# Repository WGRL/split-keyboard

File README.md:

# split-keyboard
Split keyboard with ble and usb. Custom pcb based on nrf52840 mcu module with specific firmware written in  C (Zephyr)

# Firmware
All the firmware is stored in `software` directory. It also contains all the configs for Zephyr, Kconfig, CMAKE, scripts etc.
The source code is stored in `software/src`.

The right side connects to the left one using Bluetooth. It sends the hid codes of clicked keys with approximately 12 ms intervals.
The left side takes together keys clicked on left and right side and sends it to the PC using eithter Bluetooth or USB.
USB and Bluetooth are automatically switched. If the USB connection is detected it is a chosen communication method. If there is no USB connection then left side starts Bluetooth advertising or automatically connects to the PC if there is bonding already.

The name of the device is automatically WGRL_KEYBOARD, but you can change it in `software/config/prj_left.conf` in the `# Names` section.  

# Compilation
To program the mcu you use eithter
`./scripts/run.sh left` or `./scripts/run.sh right` 
depending on the side

# Electronics
The files for printed PCBs are stored in `hardware` directory.

This is for personal use so note that the boards don't have any ESD, reverse polarity, overvoltage protection etc.
Also it lacks extra capacitor to sustain battery voltage.

# PCB
Printed PCBs. The files are in `hardware` directory. They are based on only THT elements for easier soldering.

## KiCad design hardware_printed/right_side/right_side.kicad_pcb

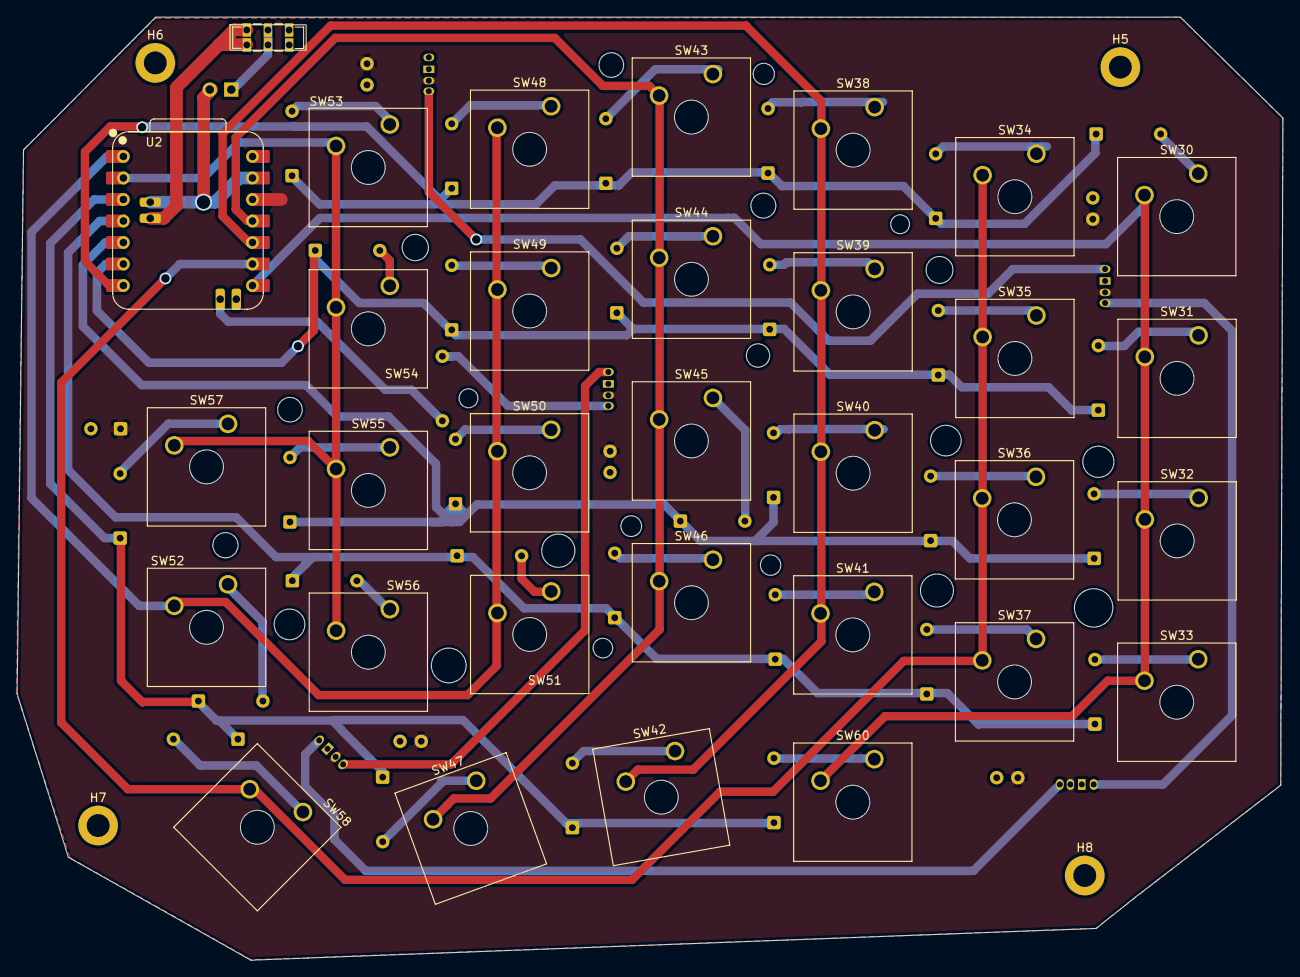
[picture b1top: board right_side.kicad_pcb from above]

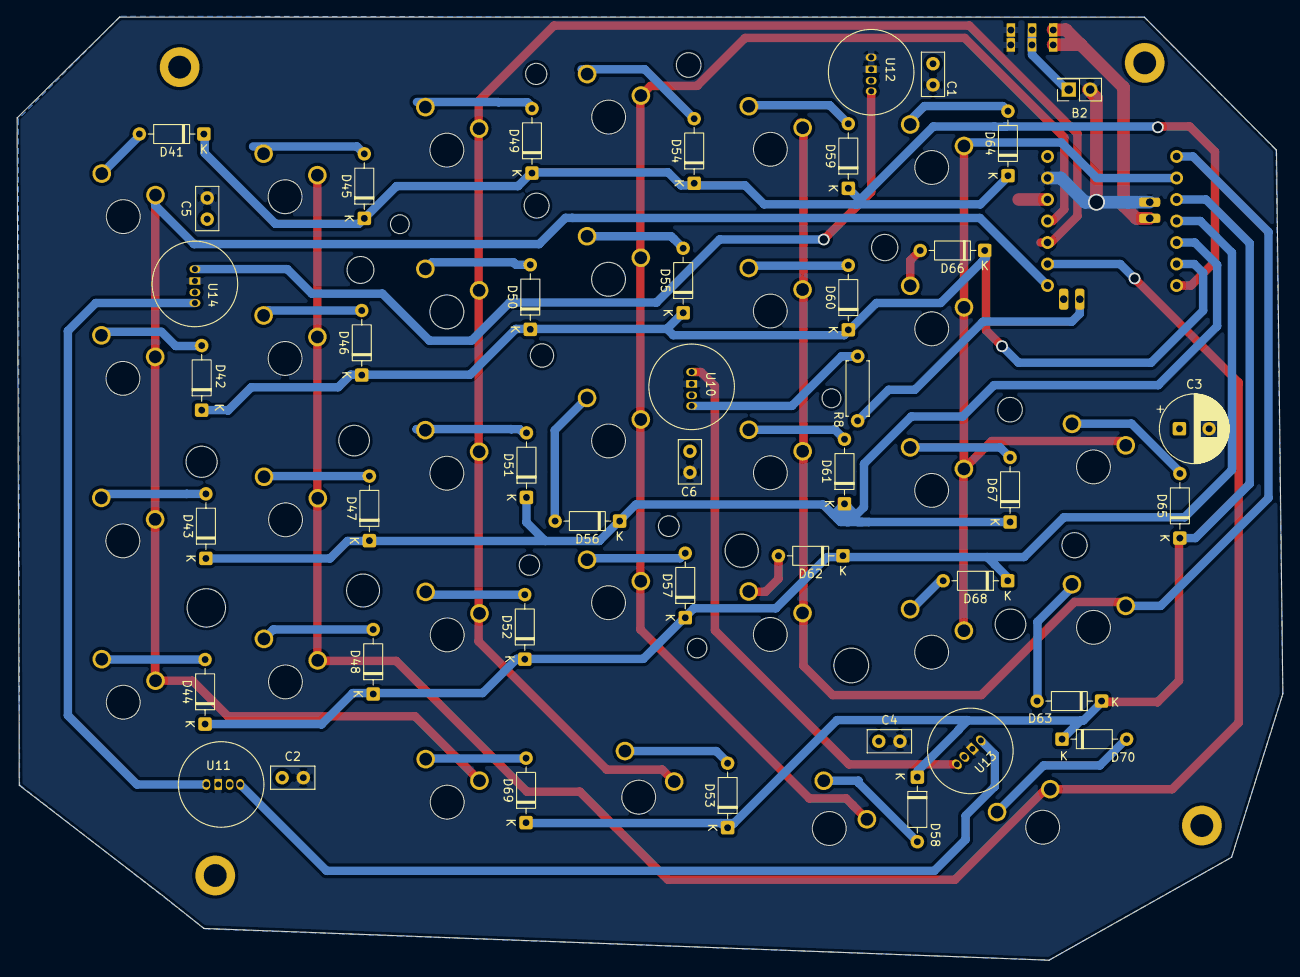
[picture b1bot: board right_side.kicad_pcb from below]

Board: 2 copper layers, 149.4 x 111.3 mm, 79 parts (43 on the bottom side), 51 nets.

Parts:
B2: Li-Pol Battery; PinSocket_2x01_P2.54mm_Vertical
C1, C2, C4, C5, C6: 100n; C_Disc_D5.0mm_W2.5mm_P2.50mm
C3: 470u; CP_Radial_D8.0mm_P3.50mm
D41, D42, D43, D44, D45, D46, D47, D48, D49, D50, D51, D52, D53, D54, D55, D56, D57, D58, D59, D60, D61, D62, D63, D64, D65, D66, D67, D68, D69, D70: 1N4148; D_DO-35_SOD27_P7.62mm_Horizontal
H5, H6, H7, H8: MountingHole; MountingHole_2.7mm_M2.5_DIN965_Pad
R8: 100; R_Axial_DIN0207_L6.3mm_D2.5mm_P7.62mm_Horizontal
SW30, SW31, SW32, SW33, SW34, SW35, SW36, SW37, SW38, SW39, SW40, SW41, SW42, SW43, SW44, SW45, SW46, SW47, SW48, SW49, SW50, SW51, SW52, SW53, SW54, SW55, SW56, SW57, SW58, SW60: SW_Push; SW_Cherry_MX_1.00u_Plate
SW_POW2: SS22T25; slider
U2: XIAO-nRF52840-DIP_SMD
U10, U11, U12, U13, U14: PL9823; PL9823-F8

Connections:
3V3: C1.1, C2.1, C3.1, C4.1, C5.1, C6.1, U2.12 (3V3), U10.3 (VDD), U11.3 (VDD), U12.3 (VDD), U13.3 (VDD), U14.3 (VDD)
/LED DIN: R8.1, U2.21 (NFC_0.09)
/col0: SW30.2, SW31.2, SW32.2, SW33.2, SW60.2, U2.8 (P1.12_D7_RX)
/col1: SW34.2, SW35.2, SW36.2, SW37.2, SW58.2, U2.9 (P1.13_D8_SCK)
/col2: SW38.2, SW39.2, SW40.2, SW41.2, SW42.2, U2.10 (P1.14_D9_MISO)
/col3: SW43.2, SW44.2, SW45.2, SW46.2, SW47.2, U2.11 (P1.15_D10_MOSI)
/col4: SW48.2, SW49.2, SW50.2, SW51.2, SW52.2, U2.1 (P0.02_A0_D0)
/col5: SW53.2, SW54.2, SW55.2, SW56.2, SW57.2, U2.2 (P0.03_A1_D1)
/row0: D41.1 (K), D45.1 (K), D49.1 (K), D54.1 (K), D59.1 (K), D64.1 (K), U2.7 (P1.11_D6_TX)
/row1: D42.1 (K), D46.1 (K), D50.1 (K), D55.1 (K), D60.1 (K), D66.1 (K), U2.6 (P0.05_A5_D5_SCL)
/row2: D43.1 (K), D47.1 (K), D51.1 (K), D56.1 (K), D61.1 (K), D67.1 (K), U2.5 (P0.04_A4_D4_SDA)
/row3: D44.1 (K), D48.1 (K), D52.1 (K), D57.1 (K), D62.1 (K), D68.1 (K), U2.4 (P0.29_A3_D3)
/row4: D53.1 (K), D58.1 (K), D63.1 (K), D65.1 (K), D69.1 (K), D70.1 (K), U2.3 (P0.28_A2_D2)
BAT+: SW_POW2.3 (A), U2.19 (BAT+)
GND: B2.2, C1.2, C2.2, C3.2, C4.2, C5.2, C6.2, SW_POW2.1 (C), U2.13 (GND), U2.20 (BAT-), U10.1 (GND), U11.1 (GND), U12.1 (GND), U12.2 (DO), U13.1 (GND), U14.1 (GND)
unnamed: B2.1, SW_POW2.2 (B)
unnamed: D41.2 (A), SW30.1
unnamed: D42.2 (A), SW31.1
unnamed: D43.2 (A), SW32.1
unnamed: D44.2 (A), SW33.1
unnamed: D45.2 (A), SW34.1
unnamed: D46.2 (A), SW35.1
unnamed: D47.2 (A), SW36.1
unnamed: D48.2 (A), SW37.1
unnamed: D49.2 (A), SW38.1
unnamed: D50.2 (A), SW39.1
unnamed: D51.2 (A), SW40.1
unnamed: D52.2 (A), SW41.1
unnamed: D53.2 (A), SW42.1
unnamed: D54.2 (A), SW43.1
unnamed: D55.2 (A), SW44.1
unnamed: D56.2 (A), SW45.1
unnamed: D57.2 (A), SW46.1
unnamed: D58.2 (A), SW47.1
unnamed: D59.2 (A), SW48.1
unnamed: D60.2 (A), SW49.1
unnamed: D61.2 (A), SW50.1
unnamed: D62.2 (A), SW51.1
unnamed: D63.2 (A), SW52.1
unnamed: D64.2 (A), SW53.1
unnamed: D65.2 (A), SW57.1
unnamed: D66.2 (A), SW54.1
unnamed: D67.2 (A), SW55.1
unnamed: D68.2 (A), SW56.1
unnamed: D69.2 (A), SW60.1
unnamed: D70.2 (A), SW58.1
unnamed: R8.2, U10.4 (DIN)
unnamed: U10.2 (DO), U13.4 (DIN)
unnamed: U11.4 (DIN), U13.2 (DO)
unnamed: U11.2 (DO), U14.4 (DIN)
unnamed: U12.4 (DIN), U14.2 (DO)

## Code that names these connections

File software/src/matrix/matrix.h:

#ifndef MATRIX_H
#define MATRIX_H

#include "../bus/bus.h"
#include <inttypes.h>
#include <stdint.h>
#include <zephyr/drivers/gpio.h>
#include <zephyr/kernel.h>
#include <zephyr/logging/log.h>
#include <zephyr/sys/printk.h>

#define ROW1_NODE DT_ALIAS(row1)
#define ROW2_NODE DT_ALIAS(row2)
#define ROW3_NODE DT_ALIAS(row3)
#define ROW4_NODE DT_ALIAS(row4)
#define ROW5_NODE DT_ALIAS(row5)

#define COL1_NODE DT_ALIAS(col1)
#define COL2_NODE DT_ALIAS(col2)
#define COL3_NODE DT_ALIAS(col3)
#define COL4_NODE DT_ALIAS(col4)
#define COL5_NODE DT_ALIAS(col5)
#define COL6_NODE DT_ALIAS(col6)

#define X_SIZE ROW_SIZE
#define Y_SIZE COL_SIZE

// gpio defs
extern const struct gpio_dt_spec row1;
extern const struct gpio_dt_spec row2;
extern const struct gpio_dt_spec row3;
extern const struct gpio_dt_spec row4;
extern const struct gpio_dt_spec row5;

extern const struct gpio_dt_spec col1;
extern const struct gpio_dt_spec col2;
extern const struct gpio_dt_spec col3;
extern const struct gpio_dt_spec col4;
extern const struct gpio_dt_spec col5;
extern const struct gpio_dt_spec col6;

extern int values_table[Y_SIZE][X_SIZE];

struct matrix {
  struct gpio_dt_spec rows[ROW_SIZE];
  struct gpio_dt_spec cols[COL_SIZE];
};

// handlers
void scan_all(struct matrix *mtx);

void keyboard_task(void *p1, void *p2, void *p3);

void scan_row(struct matrix *mtx, int num);

void process_click(struct pos *position);
#endif
